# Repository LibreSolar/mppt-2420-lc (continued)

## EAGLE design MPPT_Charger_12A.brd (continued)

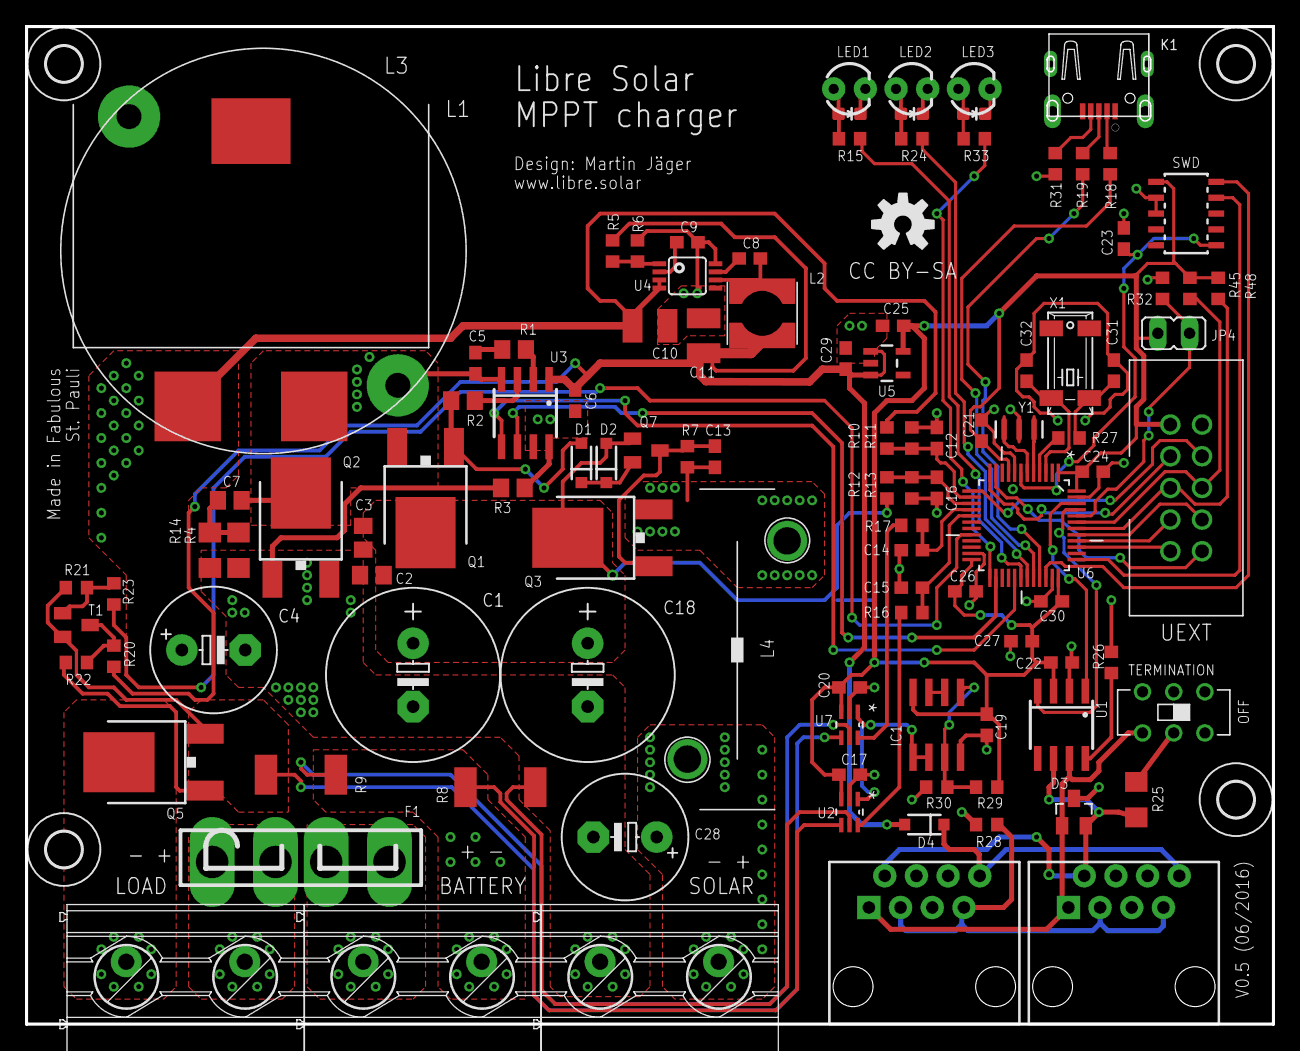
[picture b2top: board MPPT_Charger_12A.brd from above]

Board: 2 copper layers, 100.0 x 80.0 mm, 113 parts (0 on the bottom side), 77 nets.

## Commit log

2016-06-05 Initial commit of schematic and board
2016-06-05 PDF/PNG of schematic/board files uploaded
2016-06-05 Update of PDF
2016-06-05 Fixed clearance at some vias (DRC error)
2016-07-28 Foto of board uploaded
2016-12-13 Updated revision with 20A charge current
2016-12-17 Minor changes + nice image from Aisler.net
2017-01-17 Fixing issues #12 and #11
2017-03-22 Rev 0.7: moved to KiCAD
2017-03-22 Removed temporary files from repository.
2017-03-25 Library added as sub-module
2017-03-26 Updated R/C/L symbols to IEC 60617 style
2017-08-06 Updated revision: 0.8
2017-08-15 Minor changes and gerber export update
2017-11-29 rename files (append _lowercase)
2017-11-29 V0.8.1: Small changes and update to new kicad symbol library table (nightlies only)
2017-11-29 change of schematic to lowercase (_lowercase appended)
2017-11-29 Change of schematic file name to lowercase
2017-12-03 Bus power supply from battery instead of 10V rail
2017-12-11 Revision 0.9 for first small production batch - Switchable power supply for bus and UEXT (to be make sure to reach very low power consumption during LVD conditions) - MLCCs for EMC added to each high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
2017-12-11 BOM updated
2018-01-18 Final version for Jan/2018 production
2018-01-26 Adjustments to use MP2459 as SMPS (previous one out of stock)
2018-01-26 Power supply inductor changed to Tayo Yuden
2018-05-12 Update to KiCad 5 schematic library
2018-05-12 BOM update
2019-03-05 Create LM5107.pdf
    Adding main components datasheets
2019-10-05 Note regarding development of new version added
